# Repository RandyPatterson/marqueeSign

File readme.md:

# Scrolling Text Sign
WiFi Connected Marquee Sign.  

Connections

Uses this P3 Led Panel on [Amazon](https://www.amazon.com/gp/product/B079JSKF21/ref=ppx_yo_dt_b_asin_title_o09_s00?ie=UTF8&psc=1)
## Content

| Directory | Notes |
|-----------|-------| 
\src |  Source Code for ESP32 using PlatformIO.
\KiCad | Optional PCB to wrangle all of the connections required for the display

Sign exposes an API to retrieve the current message and set the next message 

| Verb | Url | Notes |
|------|-----|-------|
| GET | /message | Gets the current message displayed on the sign |
| POST | /message | Sets the next message to display.  Will change after the current message has finished scrolling |
| GET | / | OpenAPI (swagger) UI for testing and discovery |

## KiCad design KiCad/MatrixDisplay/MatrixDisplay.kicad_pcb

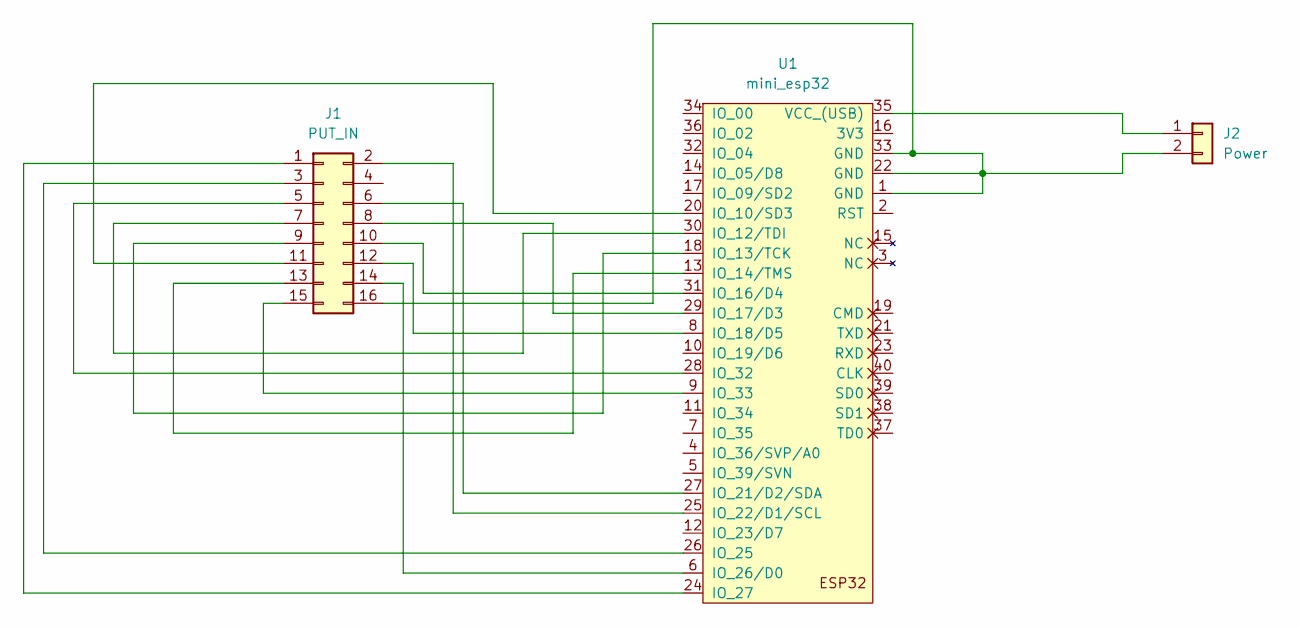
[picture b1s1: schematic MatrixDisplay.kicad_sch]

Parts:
J1: PUT_IN; PinSocket_2x08_P2.54mm_Vertical
J2: Power; PhoenixContact_GMSTBVA_2,5_2-G_1x02_P7.50mm_Vertical
U1: mini_esp32; ESP32_mini

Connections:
unnamed: J1.1, U1.24 (IO_27)
unnamed: J1.2, U1.25 (IO_22/D1/SCL)
unnamed: J1.3, U1.26 (IO_25)
unnamed: J1.5, U1.28 (IO_32)
unnamed: J1.6, U1.27 (IO_21/D2/SDA)
unnamed: J1.7, U1.30 (IO_12/TDI)
unnamed: J1.8, U1.29 (IO_17/D3)
unnamed: J1.10, U1.31 (IO_16/D4)
unnamed: J1.12, U1.8 (IO_18/D5)
unnamed: J1.14, U1.6 (IO_26/D0)
unnamed: J1.16, J2.2, U1.1 (GND), U1.22 (GND), U1.33 (GND)
unnamed: J2.1, U1.35 (VCC_(USB))
unnamed: J1.15, U1.9 (IO_33)
unnamed: J1.13, U1.13 (IO_14/TMS)
unnamed: J1.9, U1.18 (IO_13/TCK)
unnamed: J1.11, U1.20 (IO_10/SD3)

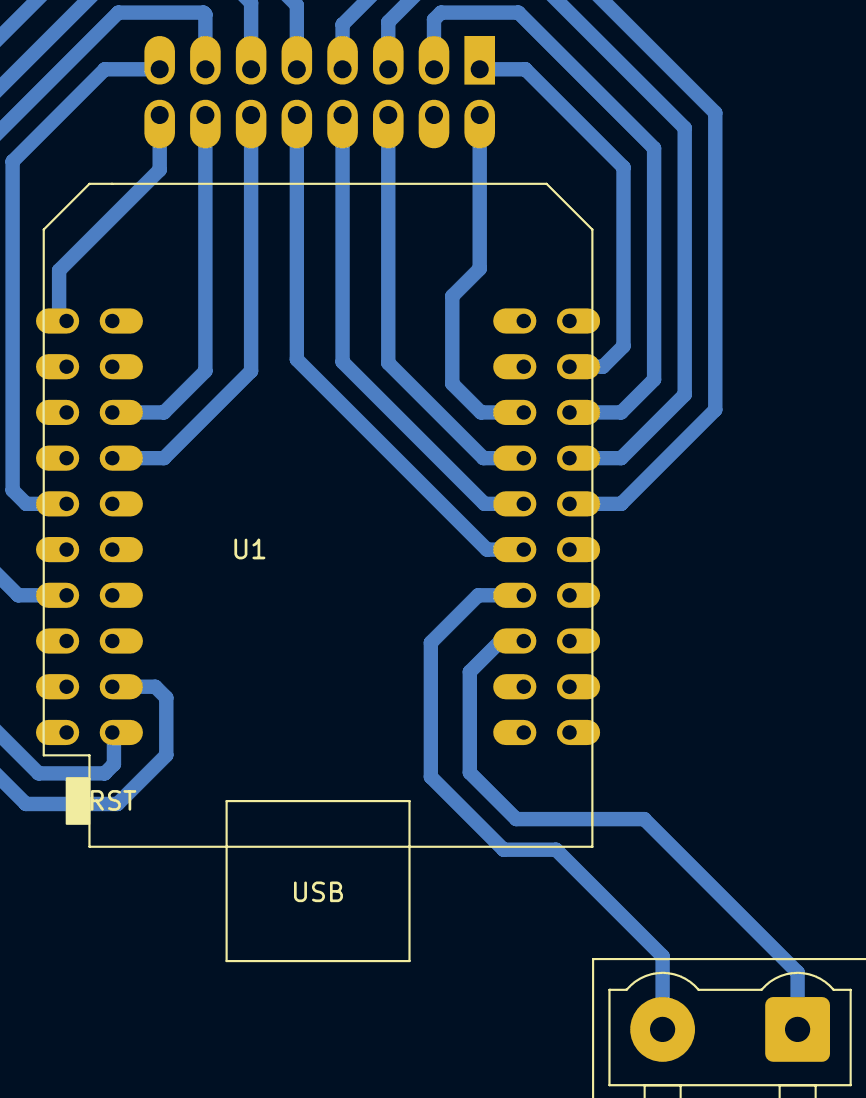
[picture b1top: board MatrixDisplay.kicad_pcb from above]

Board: 2 copper layers, 3 parts (1 on the bottom side), 16 nets.

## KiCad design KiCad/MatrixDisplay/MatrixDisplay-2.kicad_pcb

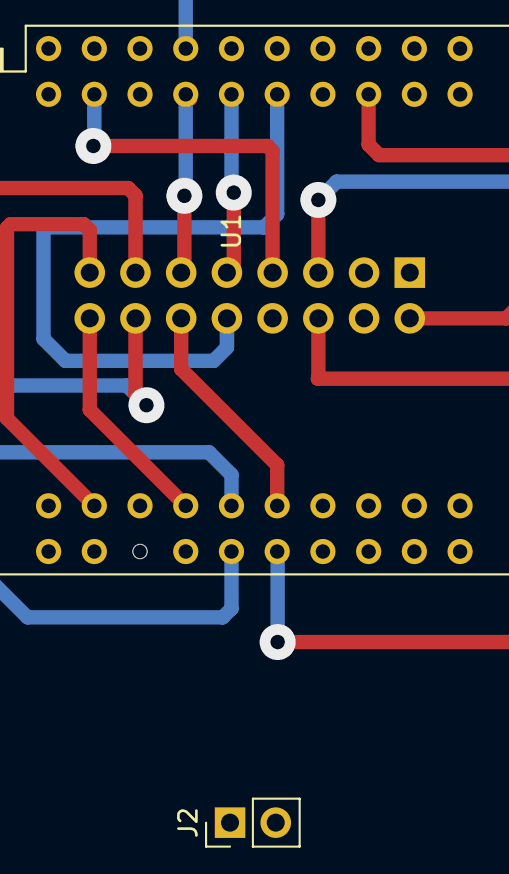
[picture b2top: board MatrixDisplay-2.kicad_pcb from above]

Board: 2 copper layers, 3 parts (1 on the bottom side), 16 nets.

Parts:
J1: PUT_IN; PinSocket_2x08_P2.54mm_Vertical
J2: Power; PinHeader_1x02_P2.54mm_Vertical
U1: mini_esp32; ESP32_mini

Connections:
unnamed: J1.1, U1.26 (IO_25)
unnamed: J1.2, U1.6 (IO_26/D0)
unnamed: J1.3, U1.24 (IO_27)
unnamed: J1.5, U1.13 (IO_14/TMS)
unnamed: J1.6, U1.30 (IO_12/TDI)
unnamed: J1.7, U1.18 (IO_13/TCK)
unnamed: J1.9, U1.12 (IO_23/D7)
unnamed: J1.10, U1.10 (IO_19/D6)
unnamed: J1.11, U1.14 (IO_05/D8)
unnamed: J1.12, U1.29 (IO_17/D3)
unnamed: J1.13, U1.31 (IO_16/D4)
unnamed: J1.14, U1.32 (IO_04)
unnamed: J1.15, U1.37 (TD0)
unnamed: J1.4, J1.16, U1.33 (GND)
unnamed: J2.1, U1.35 (VCC_(USB))
unnamed: J2.2, U1.1 (GND), U1.22 (GND)

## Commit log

2022-04-14 gifs
2022-04-14 working basic text scroll
2022-04-16 Added multi color text. Added change text API
2022-04-21 add KiCad files
2022-04-22 pinout for bodged adapter
2022-04-23 updated pinout used for PCB Adapter
2022-04-26 add wifi setup instructins to display
2022-04-26 updated font
2022-04-27 update swagger files
2022-05-02 Add readme.md
2022-05-02 fix readme
2022-05-15 initial code for animated Giff
2022-05-16 Add short annimation between messages
2022-05-16 Added optional serial messages for debug
2022-05-16 Move Giff Annimation routines into a helper class
2022-05-16 add ability to receive new message while annimation is playing
2022-05-17 minor refactoring
